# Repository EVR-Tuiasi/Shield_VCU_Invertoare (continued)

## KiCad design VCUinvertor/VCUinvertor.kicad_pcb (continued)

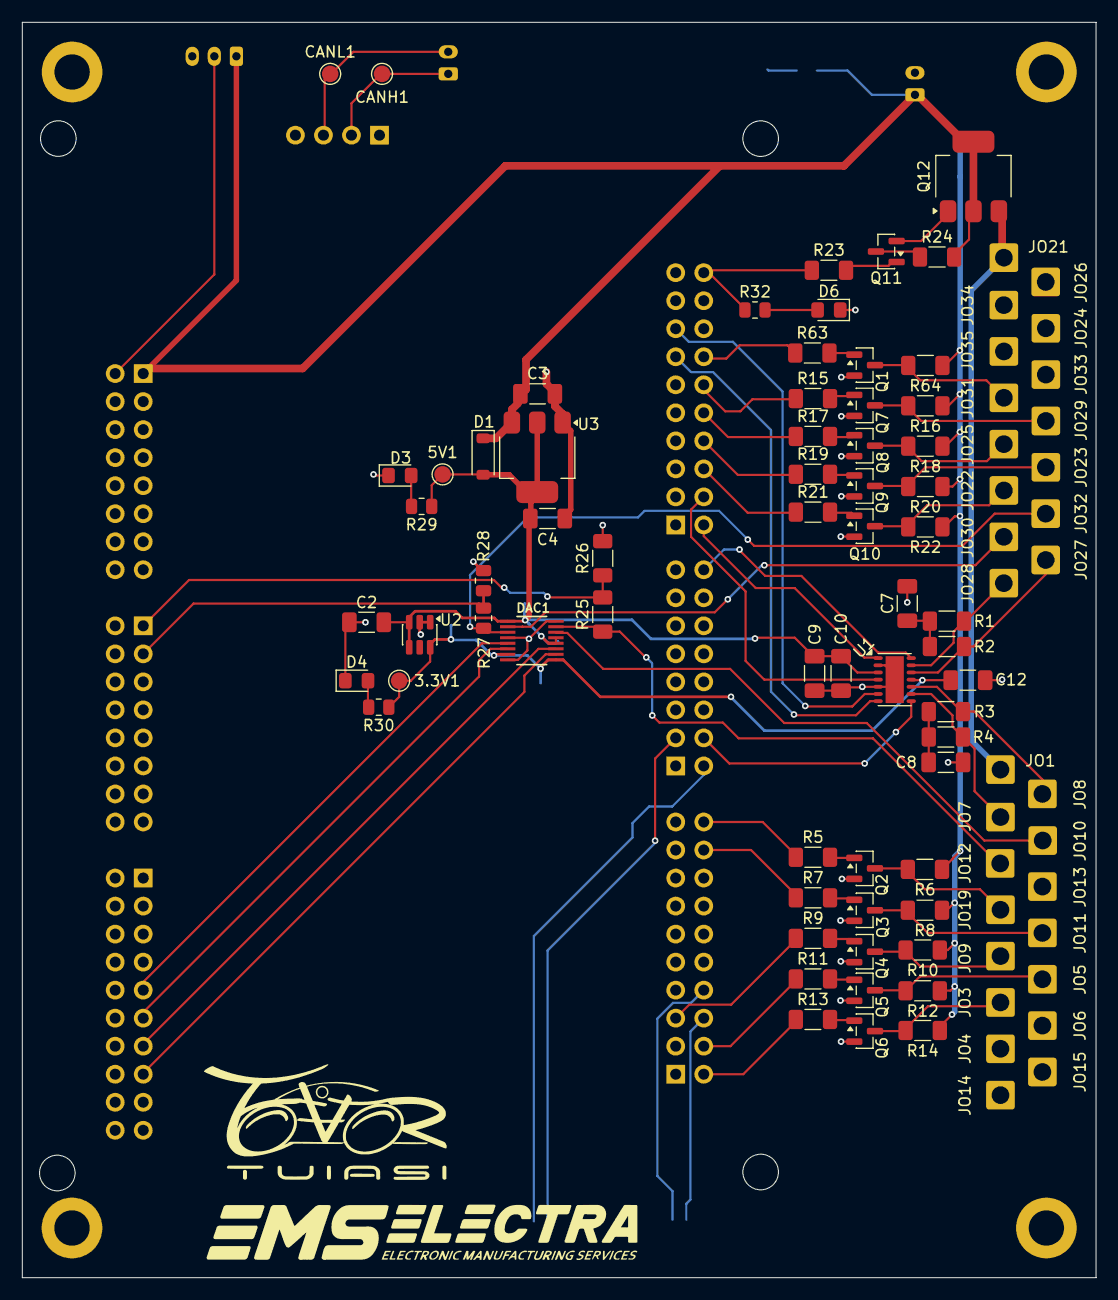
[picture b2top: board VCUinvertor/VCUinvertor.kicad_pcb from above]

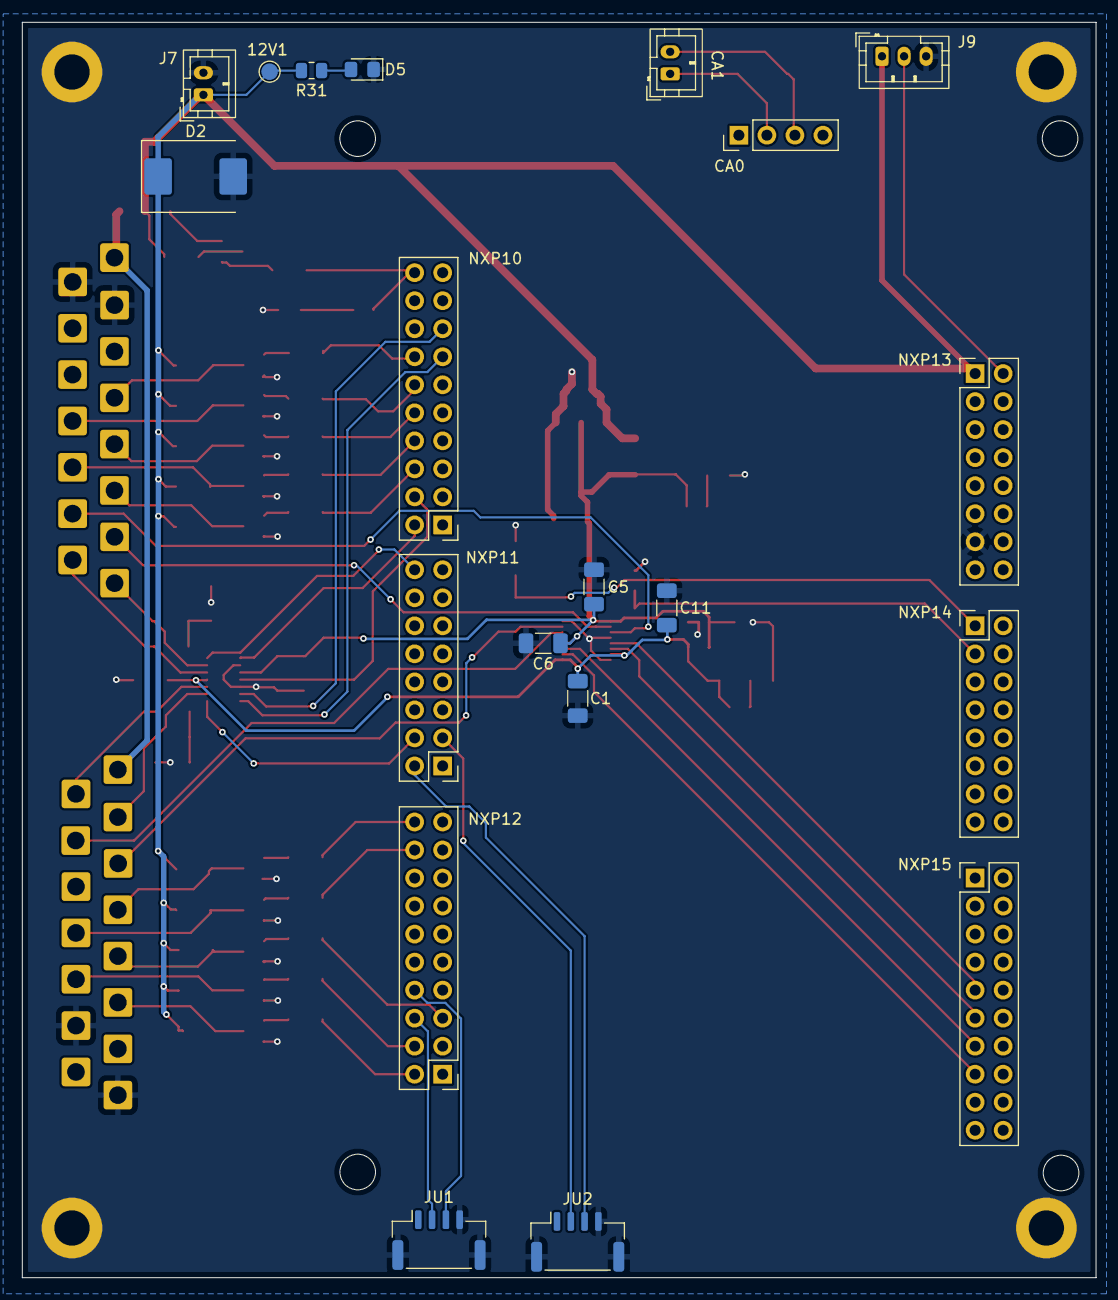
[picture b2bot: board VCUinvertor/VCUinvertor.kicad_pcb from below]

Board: 2 copper layers, 97.3 x 113.8 mm, 119 parts (20 on the bottom side), 72 nets.

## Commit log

2026-03-26 Scheme added
2026-03-27 Layout_Invertor2
2026-03-28 NMOS_Simulation_Selection
2026-03-28 Footprint assignment
2026-03-29 Layout_Global arrangement
2026-03-29 DAQ footprint correction
2026-03-30 New PMOS config for switching
2026-03-30 VCU_PinCorrection_0.1
2026-03-30 Pin_Assignment_Main_Done
    [15:48, 3/30/2026] Viorel VCU: ptb22 - j12 - pin 1 - LPUART1_TX - UART_INV01 pin 3
    ptb23 - j12 - pin 3 - LPUART1_RX - UART_INV01 pin 2
    ptd2 - j11 - pin 5 - LPUART3_TX - UART_INV02 pin 3
    ptd3 - j11 - pin 7 - LPUART3_RX - UART_INV01 pin 2
    [15:55, 3/30/2026] Viorel VCU: pte23 - j15 - pin 9 - EMIOS1_CH3_H - PWM_NXP1
    pte24 - j15 - pin 11 - EMIOS1_CH4_H - PWM_NXP2
2026-03-30 FirstLayout_Completed
2026-03-31 Pyy & Pzz pin assignment
2026-03-31 Added datasheets for MOS
2026-04-01 LastCorrection_ToBeChecked
2026-04-01 Logo_added
2026-04-01 Block diagram cleanup
2026-04-01 BOM csv added
2026-04-04 Changes on Supply
    1.Protection shottky diode added
    2.Separate supply for INV via Darlington (1A Max.)
    3.Control of the supply from J10 Pin 20 for INV supply - added
2026-04-04 BOM + Gerbers - added
2026-04-06 SMD components resized for Handsoldering (0805 -> 1206)
    *Resistors & Capacitors are now upgraded to size 1206 for easy handsoldering
2026-04-06 Gerber for bigSMD added
2026-04-07 TestPoints added
2026-04-07 Ref LEDs added
    For 3.3V & 5V & ...
    Added for easy testing, LEDs running 2-3 mA each
2026-04-07 Folders_smallManagement
2026-04-08 DAC1 - 3D model added
2026-04-24 Corrections on UART01/02
2026-04-26 Board - resized + Hole corrections
2026-04-27 INV wires displacement change
    Some connections were brought closer to their control pin
2026-04-27 Corrections wiring Brake_light
2026-04-28 Redid layout for CAN and DAC chips
2026-04-28 CleanUp after changes
2026-04-28 12V -> BAT+
2026-04-29 DAC - cap location correction
2026-04-29 History file ignored
2026-04-29 Redid reverse polarity protection
2026-04-29 Supply GND small correction
2026-04-30 Dorlington -> Relay for INV_OFF
2026-05-09 Simulations_continued
2026-05-11 Relay NC to NO change
2026-05-11 Changes on NXPTPSOUT1&2
    1. Switch The switch to NO from NC --> From pin 2 to pin 4
    2.Move the connectors of the TPS OUT1 & 2
2026-05-11 Error corrections - Done
2026-05-13 Small drawing correction
2026-05-14 STEP file added
2026-05-18 MOS pulldown + missing INV pins added
2026-05-19 Wire labels correction
2026-05-26 Revision author added
2026-06-01 Corrections + PUMP&FAN circuit 0.1
2026-06-01 PCB Layout with FAN&PUMP MOS - Done
2026-06-03 Hole_mounting displacement correction
2026-06-04 INV pinout+ layout changes - Done
2026-06-04 Board silkscreen corrections for visibility
2026-06-05 FAN&PUMP pin change
2026-06-06 Pin - GND assignment
2026-06-06 Check on BC848C
2026-06-07 Mounting Holes + Relay Flyback added
2026-06-08 Connectors 2.0mm -> 2.5mm correction
2026-06-10 FAN MOS correction D->S
2026-06-14 Gate Driver MOS added + layout done
2026-06-14 CAN_IN + CAN_OUT added
2026-06-17 Prototype tested for FAN control
2026-06-20 TEMP/PRESSURE ctrl schematic - proto
2026-06-21 CAN: TJA1448 Footprint correction
2026-06-21 Changed resistor footprints to 1206
2026-06-22 BOM - added
2026-06-23 Small optimisations, added jumper for CAN transciever VIO
2026-06-23 Thickened traces for fans, pumps and inverter supply
2026-06-23 Redid connection for pump and fan signals
2026-06-23 Fixed violation for unconnected pin
2026-06-23 Updated BOM, two components left
2026-06-23 Changed the LED to be the same as VCU_Board
2026-06-23 Removed components that we have already from BOM
2026-06-25 Redid connections for pressure and temperature sensors
2026-06-25 LDO supply wire correction
2026-06-25 GBR - added
2026-06-26 Remove custom GND for protection
2026-06-29 GND plane small correction + new GBR - added + sent
